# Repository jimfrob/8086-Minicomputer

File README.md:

# 8086 Minicomputer
A basic minicomputer design based on the 8086 CPU

Before anyone starts poking holes in the massive gaps in the logic that Google's AI chat provided in the published documents, I have already started a Rev 2 version of this project to try to get it down to 100x100mm 2-layer boards (to make them ultra-cheap to order from PCBWay). While doing so, I uncovered MANY serious flaws in the design, including, but not limited to, the refresh timing for the DRAM. From here, I'll let my less-experienced self carry on.

Full disclosure up front: I heavily used LLM chats to help me with the design because I'm a complete noob. I just happened to have an 8086 8 MHz CPU lying about, as well as a Specialix I/O4+ quad UART serial card, and I thought I might like to build a minicomputer out of it. This idea was largely inspired by Usagi Electric's TMS9900 minicomputer project. You can check out his projects at https://github.com/Nakazoto

This is, as I've said, a minicomputer. It is my intention that one will only be able to communicate with it over serial terminal, and the serial card I have supports up to four. Storage will be handled by a fairly generic multi-I/O card built around the DLU 270. The eventual ROM code will have these cards in mind. Simply because it's what I have on hand that's 16-bit native, I've gone with the AM27C400 EPROM.

I'm providing the KiCad files I have developed for anyone to use, modify, whatever. I'm quite open to any helpful tips for improving the design. My only minor request is that anyone who makes changes makes sure those changes make it into the wild for everyone to enjoy.

There is absolutely no ROM code at the moment because I don't know any 8086 assembly. I'll be having to learn on the fly. Because of the sheer size of the EPROM, it's entirely possible that I may end up putting the whole OS in there, but this is still early days.

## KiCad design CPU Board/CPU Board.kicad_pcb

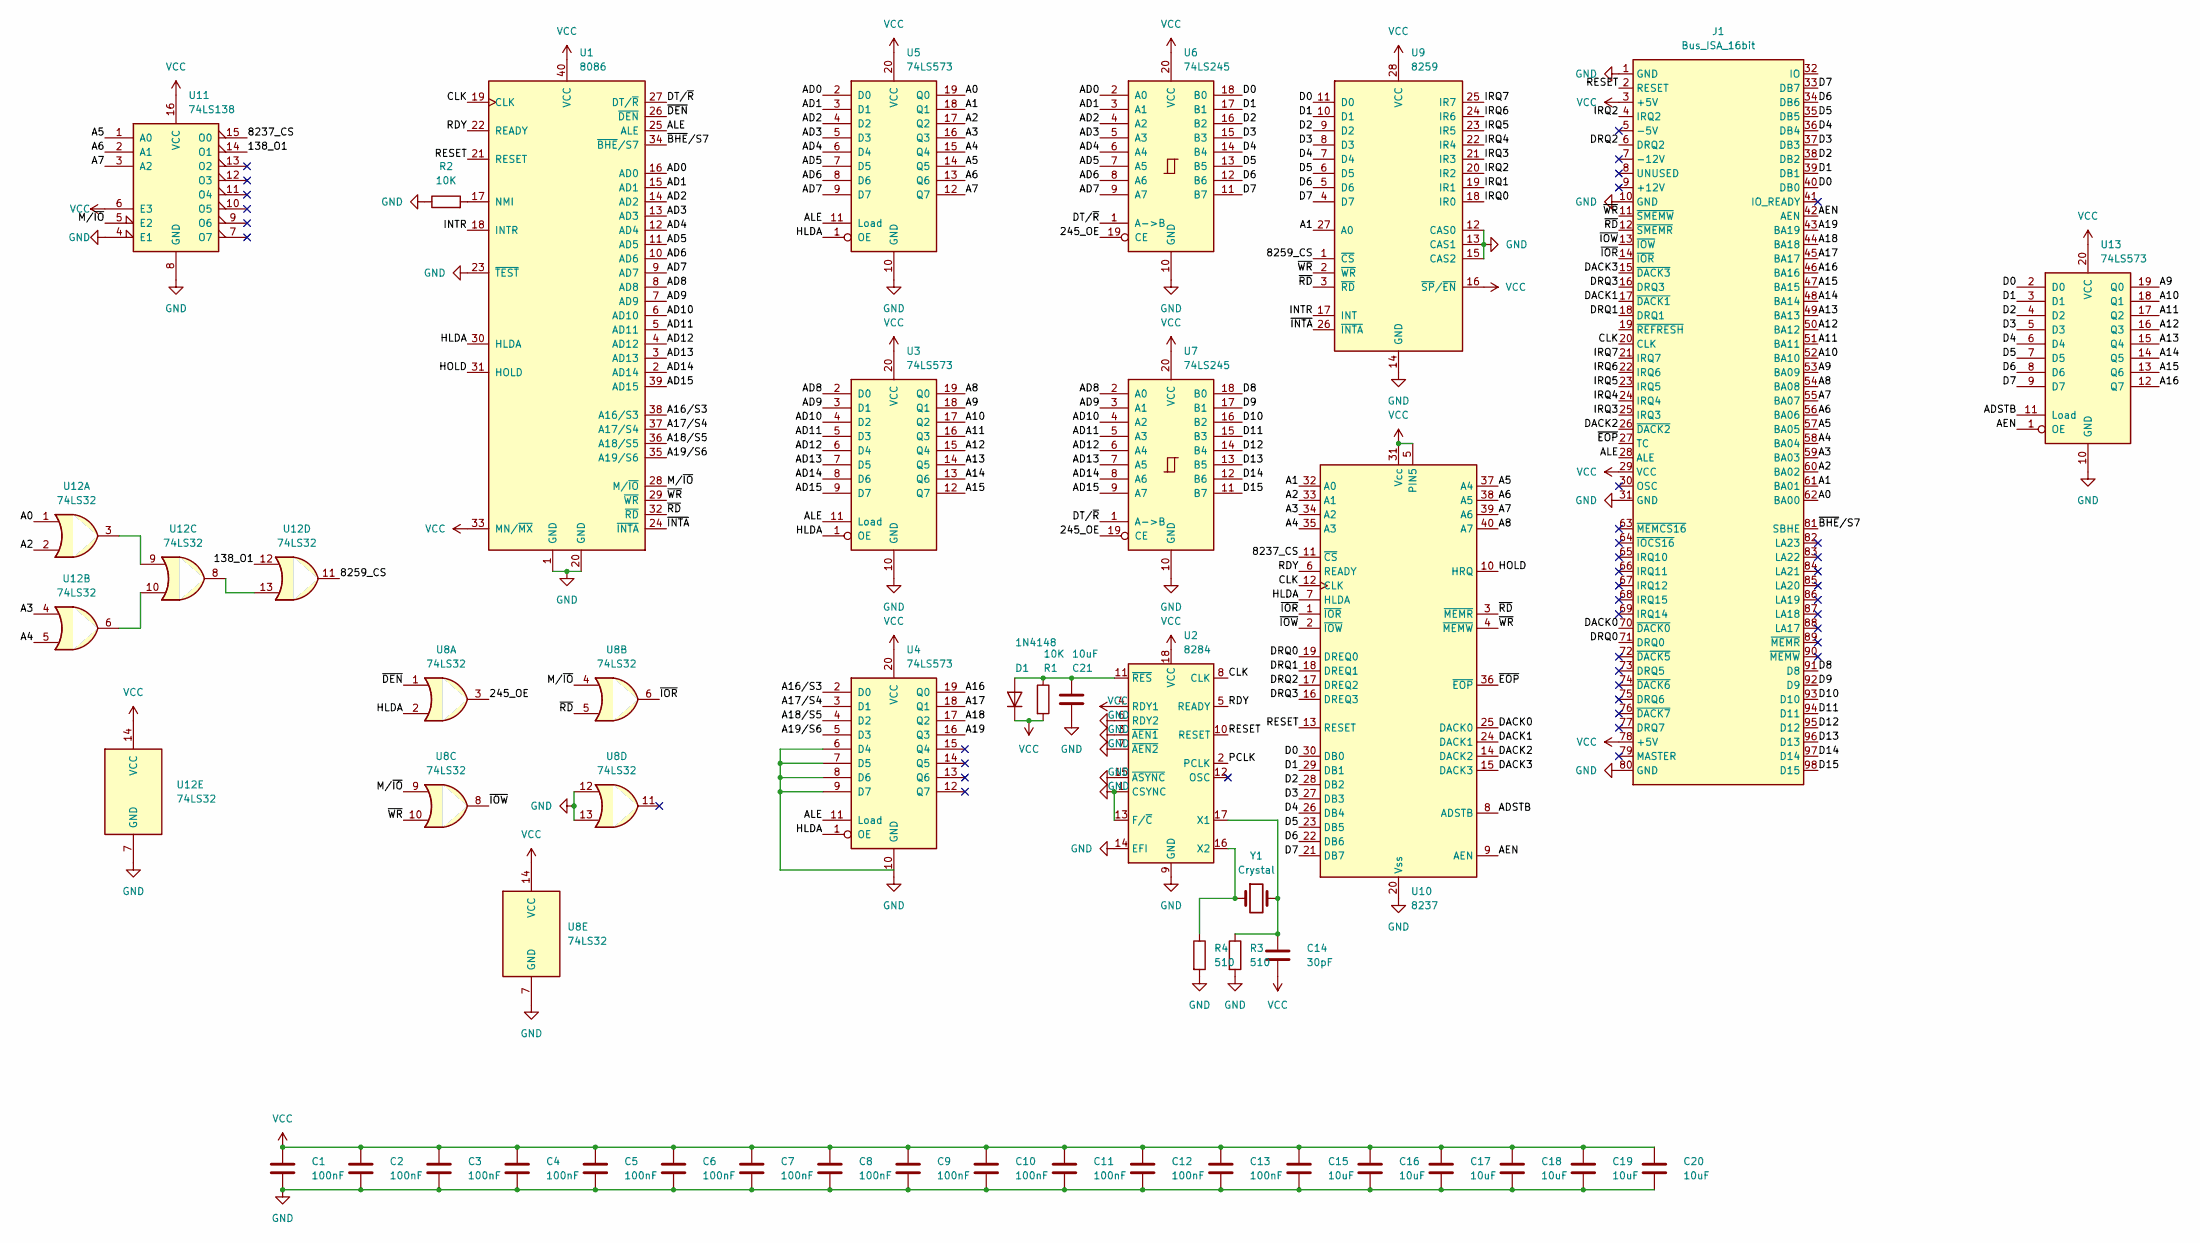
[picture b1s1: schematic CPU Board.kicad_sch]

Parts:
C1, C2, C3, C4, C5, C6, C7, C8, C9, C10, C11, C12, C13: 100nF; C_Disc_D10.0mm_W2.5mm_P5.00mm
C14: 30pF; C_Disc_D10.0mm_W2.5mm_P5.00mm
C15, C16, C17, C18, C19, C20, C21: 10uF; CP_Radial_Tantal_D5.0mm_P2.50mm
D1: 1N4148; D_A-405_P7.62mm_Horizontal
J1: Bus_ISA_16bit; BUS_AT
R1, R2: 10K; R_Axial_DIN0204_L3.6mm_D1.6mm_P7.62mm_Horizontal
R3, R4: 510; R_Axial_DIN0204_L3.6mm_D1.6mm_P7.62mm_Horizontal
U1: 8086; DIP-40_W15.24mm
U2: 8284; DIP-18_W7.62mm
U3, U4, U5, U13: 74LS573; DIP-20_W7.62mm
U6, U7: 74LS245; DIP-20_W7.62mm
U8, U12: 74LS32; DIP-14_W7.62mm
U9: 8259; DIP-28_W15.24mm
U10: 8237; DIP-40_W15.24mm
U11: 74LS138; DIP-16_W7.62mm
Y1: Crystal; Resonator-2Pin_W10.0mm_H5.0mm

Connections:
/138_O1: U11.14 (O1), U12.12
/245_OE: U6.19 (CE), U7.19 (CE), U8.3
/8237_CS: U10.11 (~CS), U11.15 (O0)
/8259_CS: U9.1 (~CS), U12.11
/A0: J1.62 (BA00), U5.19 (Q0), U12.1
/A1: J1.61 (BA01), U5.18 (Q1), U9.27 (A0), U10.32 (A0)
/A2: J1.60 (BA02), U5.17 (Q2), U10.33 (A1), U12.2
/A3: J1.59 (BA03), U5.16 (Q3), U10.34 (A2), U12.4
/A4: J1.58 (BA04), U5.15 (Q4), U10.35 (A3), U12.5
/A5: J1.57 (BA05), U5.14 (Q5), U10.37 (A4), U11.1 (A0)
/A6: J1.56 (BA06), U5.13 (Q6), U10.38 (A5), U11.2 (A1)
/A7: J1.55 (BA07), U5.12 (Q7), U10.39 (A6), U11.3 (A2)
/A8: J1.54 (BA08), U3.19 (Q0), U10.40 (A7)
/A9: J1.53 (BA09), U3.18 (Q1), U13.19 (Q0)
/A10: J1.52 (BA10), U3.17 (Q2), U13.18 (Q1)
/A11: J1.51 (BA11), U3.16 (Q3), U13.17 (Q2)
/A12: J1.50 (BA12), U3.15 (Q4), U13.16 (Q3)
/A13: J1.49 (BA13), U3.14 (Q5), U13.15 (Q4)
/A14: J1.48 (BA14), U3.13 (Q6), U13.14 (Q5)
/A15: J1.47 (BA15), U3.12 (Q7), U13.13 (Q6)
/A16: J1.46 (BA16), U4.19 (Q0), U13.12 (Q7)
/A16/S3: U1.38 (A16/S3), U4.2 (D0)
/A17: J1.45 (BA17), U4.18 (Q1)
/A17/S4: U1.37 (A17/S4), U4.3 (D1)
/A18: J1.44 (BA18), U4.17 (Q2)
/A18/S5: U1.36 (A18/S5), U4.4 (D2)
/A19: J1.43 (BA19), U4.16 (Q3)
/A19/S6: U1.35 (A19/S6), U4.5 (D3)
/AD0: U1.16 (AD0), U5.2 (D0), U6.2 (A0)
/AD1: U1.15 (AD1), U5.3 (D1), U6.3 (A1)
/AD2: U1.14 (AD2), U5.4 (D2), U6.4 (A2)
/AD3: U1.13 (AD3), U5.5 (D3), U6.5 (A3)
/AD4: U1.12 (AD4), U5.6 (D4), U6.6 (A4)
/AD5: U1.11 (AD5), U5.7 (D5), U6.7 (A5)
/AD6: U1.10 (AD6), U5.8 (D6), U6.8 (A6)
/AD7: U1.9 (AD7), U5.9 (D7), U6.9 (A7)
/AD8: U1.8 (AD8), U3.2 (D0), U7.2 (A0)
/AD9: U1.7 (AD9), U3.3 (D1), U7.3 (A1)
/AD10: U1.6 (AD10), U3.4 (D2), U7.4 (A2)
/AD11: U1.5 (AD11), U3.5 (D3), U7.5 (A3)
/AD12: U1.4 (AD12), U3.6 (D4), U7.6 (A4)
/AD13: U1.3 (AD13), U3.7 (D5), U7.7 (A5)
/AD14: U1.2 (AD14), U3.8 (D6), U7.8 (A6)
/AD15: U1.39 (AD15), U3.9 (D7), U7.9 (A7)
/ADSTB: U10.8 (ADSTB), U13.11 (Load)
/AEN: J1.42 (AEN), U10.9 (AEN), U13.1 (OE)
/ALE: J1.28 (ALE), U1.25 (ALE), U3.11 (Load), U4.11 (Load), U5.11 (Load)
/CLK: J1.20 (CLK), U1.19 (CLK), U2.8 (CLK), U10.12 (CLK)
/D0: J1.40 (DB0), U6.18 (B0), U9.11 (D0), U10.30 (DB0), U13.2 (D0)
/D1: J1.39 (DB1), U6.17 (B1), U9.10 (D1), U10.29 (DB1), U13.3 (D1)
/D2: J1.38 (DB2), U6.16 (B2), U9.9 (D2), U10.28 (DB2), U13.4 (D2)
/D3: J1.37 (DB3), U6.15 (B3), U9.8 (D3), U10.27 (DB3), U13.5 (D3)
/D4: J1.36 (DB4), U6.14 (B4), U9.7 (D4), U10.26 (DB4), U13.6 (D4)
/D5: J1.35 (DB5), U6.13 (B5), U9.6 (D5), U10.23 (DB5), U13.7 (D5)
/D6: J1.34 (DB6), U6.12 (B6), U9.5 (D6), U10.22 (DB6), U13.8 (D6)
/D7: J1.33 (DB7), U6.11 (B7), U9.4 (D7), U10.21 (DB7), U13.9 (D7)
/D8: J1.91 (D8), U7.18 (B0)
/D9: J1.92 (D9), U7.17 (B1)
/D10: J1.93 (D10), U7.16 (B2)
/D11: J1.94 (D11), U7.15 (B3)
/D12: J1.95 (D12), U7.14 (B4)
/D13: J1.96 (D13), U7.13 (B5)
/D14: J1.97 (D14), U7.12 (B6)
/D15: J1.98 (D15), U7.11 (B7)
/DACK0: J1.70 (~DACK0), U10.25 (DACK0)
/DACK1: J1.17 (~DACK1), U10.24 (DACK1)
/DACK2: J1.26 (~DACK2), U10.14 (DACK2)
/DACK3: J1.15 (~DACK3), U10.15 (DACK3)
/DRQ0: J1.71 (DRQ0), U10.19 (DREQ0)
/DRQ1: J1.18 (DRQ1), U10.18 (DREQ1)
/DRQ2: J1.6 (DRQ2), U10.17 (DREQ2)
/DRQ3: J1.16 (DRQ3), U10.16 (DREQ3)
/DT/~R: U1.27 (DT/~R), U6.1 (A->B), U7.1 (A->B)
/HLDA: U1.30 (HLDA), U3.1 (OE), U4.1 (OE), U5.1 (OE), U8.2, U10.7 (HLDA)
/HOLD: U1.31 (HOLD), U10.10 (HRQ)
/INTR: U1.18 (INTR), U9.17 (INT)
/IRQ0: U9.18 (IR0)
/IRQ1: U9.19 (IR1)
/IRQ2: J1.4 (IRQ2), U9.20 (IR2)
/IRQ3: J1.25 (IRQ3), U9.21 (IR3)
/IRQ4: J1.24 (IRQ4), U9.22 (IR4)
/IRQ5: J1.23 (IRQ5), U9.23 (IR5)
/IRQ6: J1.22 (IRQ6), U9.24 (IR6)
/IRQ7: J1.21 (IRQ7), U9.25 (IR7)
/M/~IO: U1.28 (M/~IO), U8.4, U8.9, U11.5 (E2)
/PCLK: U2.2 (PCLK)
/RDY: U1.22 (READY), U2.5 (READY), U10.6 (READY)
/RESET: J1.2 (RESET), U1.21 (RESET), U2.10 (RESET), U10.13 (RESET)
/~BHE/S7: J1.81 (SBHE), U1.34 (~BHE/S7)
/~DEN: U1.26 (~DEN), U8.1
/~EOP: J1.27 (TC), U10.36 (~EOP)
/~INTA: U1.24 (~INTA), U9.26 (~INTA)
/~IOR: J1.14 (~IOR), U8.6, U10.1 (~IOR)
/~IOW: J1.13 (~IOW), U8.8, U10.2 (~IOW)
/~RD: J1.12 (~SMEMR), U1.32 (~RD), U8.5, U9.3 (~RD), U10.3 (~MEMR)
/~WR: J1.11 (~SMEMW), U1.29 (~WR), U8.10, U9.2 (~WR), U10.4 (~MEMW)
GND: C1.2, C2.2, C3.2, C4.2, C5.2, C6.2, C7.2, C8.2, C9.2, C10.2, C11.2, C12.2, C13.2, C15.2, C16.2, C17.2, C18.2, C19.2, C20.2, C21.2, J1.1 (GND), J1.10 (GND), J1.31 (GND), J1.80 (GND), R2.1, R3.2, R4.2, U1.1 (GND), U1.20 (GND), U1.23 (~TEST), U2.1 (CSYNC), U2.3 (~AEN1), U2.6 (RDY2), U2.7 (~AEN2), U2.9 (GND), U2.13 (F/~C), U2.14 (EFI), U2.15 (~ASYNC), U3.10 (GND), U4.10 (GND), U5.10 (GND), U6.10 (GND), U7.10 (GND), U8.7 (GND), U8.12, U8.13, U9.12 (CAS0), U9.13 (CAS1), U9.14 (GND), U9.15 (CAS2), U10.20 (Vss), U11.4 (E1), U11.8 (GND), U12.7 (GND), U13.10 (GND)
unnamed: C21.1, D1.2 (A), R1.1, U2.11 (~RES)
unnamed: R2.2, U1.17 (NMI)
unnamed: C14.1, R3.1, U2.17 (X1), Y1.2
unnamed: R4.1, U2.16 (X2), Y1.1
unnamed: U4.6 (D4), U4.7 (D5), U4.8 (D6), U4.9 (D7)
unnamed: U12.3, U12.9
unnamed: U12.6, U12.10
unnamed: U12.8, U12.13
VCC: C1.1, C2.1, C3.1, C4.1, C5.1, C6.1, C7.1, C8.1, C9.1, C10.1, C11.1, C12.1, C13.1, C14.2, C15.1, C16.1, C17.1, C18.1, C19.1, C20.1, D1.1 (K), J1.3 (+5V), J1.29 (VCC), J1.78 (+5V), R1.2, U1.33 (MN/~MX), U1.40 (VCC), U2.4 (RDY1), U2.18 (VCC), U3.20 (VCC), U4.20 (VCC), U5.20 (VCC), U6.20 (VCC), U7.20 (VCC), U8.14 (VCC), U9.16 (~SP/~EN), U9.28 (VCC), U10.5 (PIN5), U10.31 (Vcc), U11.6 (E3), U11.16 (VCC), U12.14 (VCC), U13.20 (VCC)

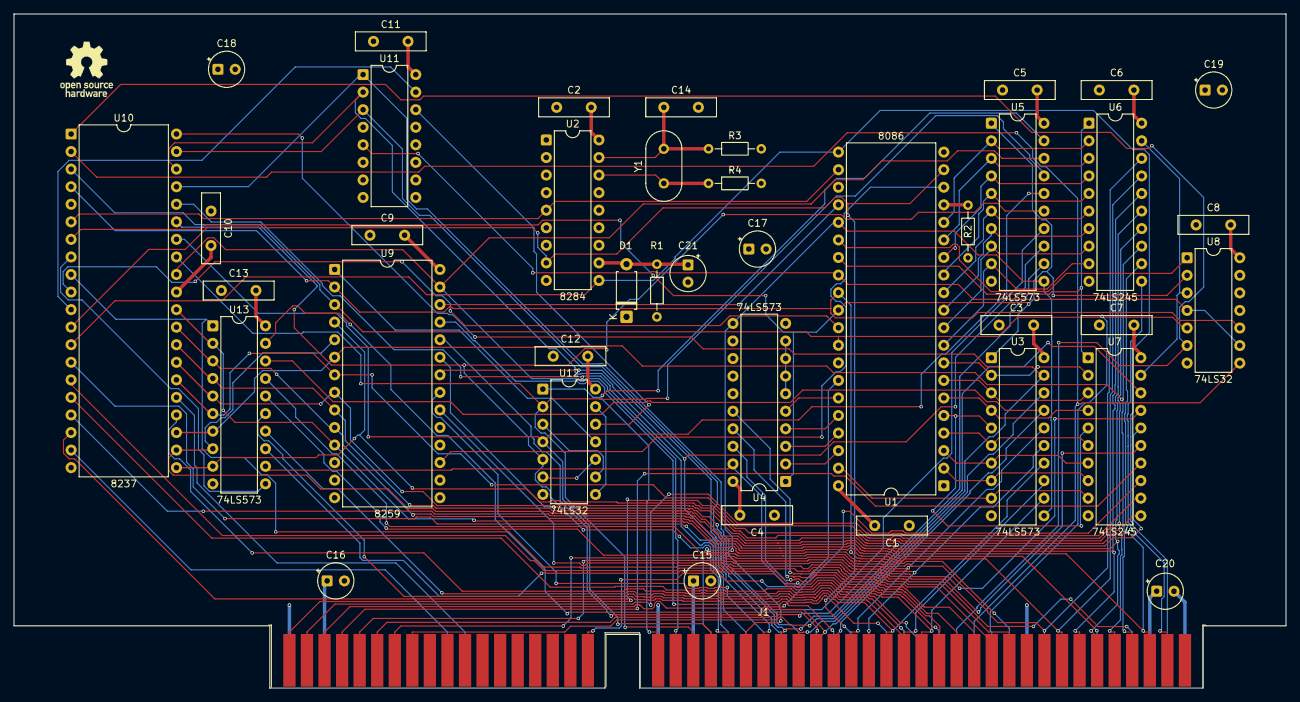
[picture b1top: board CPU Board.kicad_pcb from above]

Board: 4 copper layers, 184.0 x 97.5 mm, 41 parts (0 on the bottom side), 103 nets.

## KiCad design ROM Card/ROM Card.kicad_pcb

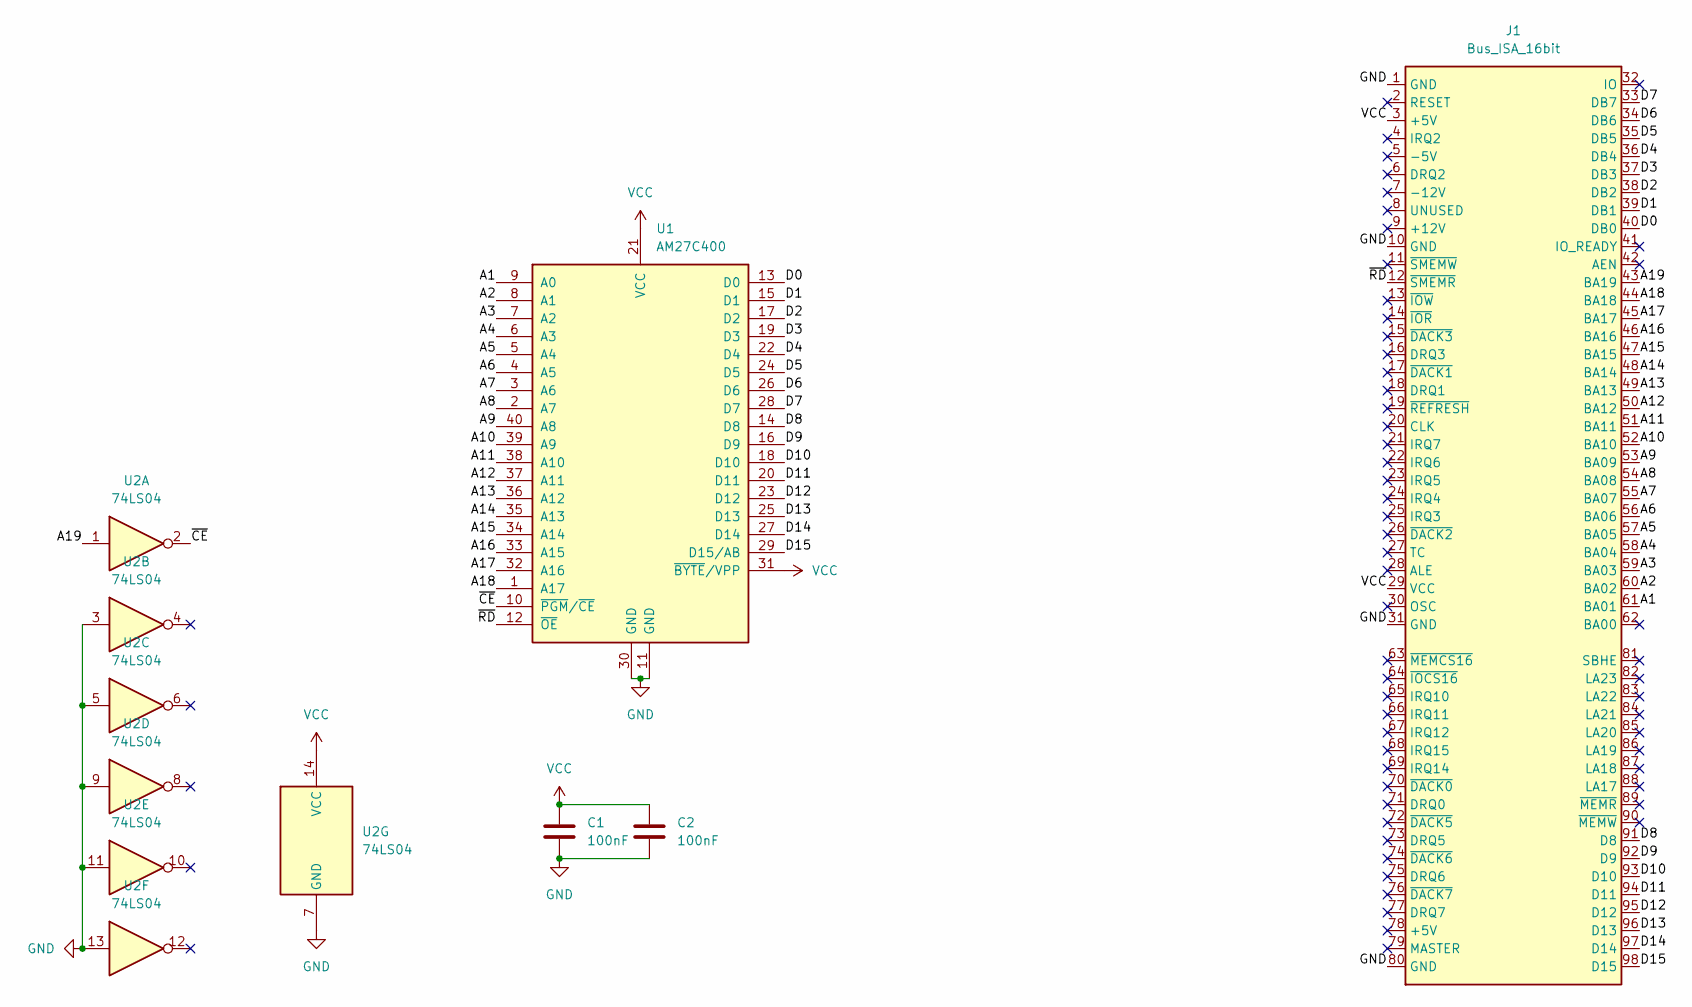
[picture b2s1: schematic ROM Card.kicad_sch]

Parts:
C1, C2: 100nF; C_Disc_D10.0mm_W2.5mm_P5.00mm
J1: Bus_ISA_16bit; BUS_AT
U1: AM27C400; DIP-40_W15.24mm
U2: 74LS04; DIP-14_W7.62mm

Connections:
/A1: J1.61 (BA01), U1.9 (A0)
/A2: J1.60 (BA02), U1.8 (A1)
/A3: J1.59 (BA03), U1.7 (A2)
/A4: J1.58 (BA04), U1.6 (A3)
/A5: J1.57 (BA05), U1.5 (A4)
/A6: J1.56 (BA06), U1.4 (A5)
/A7: J1.55 (BA07), U1.3 (A6)
/A8: J1.54 (BA08), U1.2 (A7)
/A9: J1.53 (BA09), U1.40 (A8)
/A10: J1.52 (BA10), U1.39 (A9)
/A11: J1.51 (BA11), U1.38 (A10)
/A12: J1.50 (BA12), U1.37 (A11)
/A13: J1.49 (BA13), U1.36 (A12)
/A14: J1.48 (BA14), U1.35 (A13)
/A15: J1.47 (BA15), U1.34 (A14)
/A16: J1.46 (BA16), U1.33 (A15)
/A17: J1.45 (BA17), U1.32 (A16)
/A18: J1.44 (BA18), U1.1 (A17)
/A19: J1.43 (BA19), U2.1
/D0: J1.40 (DB0), U1.13 (D0)
/D1: J1.39 (DB1), U1.15 (D1)
/D2: J1.38 (DB2), U1.17 (D2)
/D3: J1.37 (DB3), U1.19 (D3)
/D4: J1.36 (DB4), U1.22 (D4)
/D5: J1.35 (DB5), U1.24 (D5)
/D6: J1.34 (DB6), U1.26 (D6)
/D7: J1.33 (DB7), U1.28 (D7)
/D8: J1.91 (D8), U1.14 (D8)
/D9: J1.92 (D9), U1.16 (D9)
/D10: J1.93 (D10), U1.18 (D10)
/D11: J1.94 (D11), U1.20 (D11)
/D12: J1.95 (D12), U1.23 (D12)
/D13: J1.96 (D13), U1.25 (D13)
/D14: J1.97 (D14), U1.27 (D14)
/D15: J1.98 (D15), U1.29 (D15/AB)
/~CE: U1.10 (~PGM/~CE), U2.2
/~RD: J1.12 (~SMEMR), U1.12 (~OE)
GND: C1.2, C2.2, J1.1 (GND), J1.10 (GND), J1.31 (GND), J1.80 (GND), U1.11 (GND), U1.30 (GND), U2.3, U2.5, U2.7 (GND), U2.9, U2.11, U2.13
VCC: C1.1, C2.1, J1.3 (+5V), J1.29 (VCC), U1.21 (VCC), U1.31 (~BYTE/VPP), U2.14 (VCC)

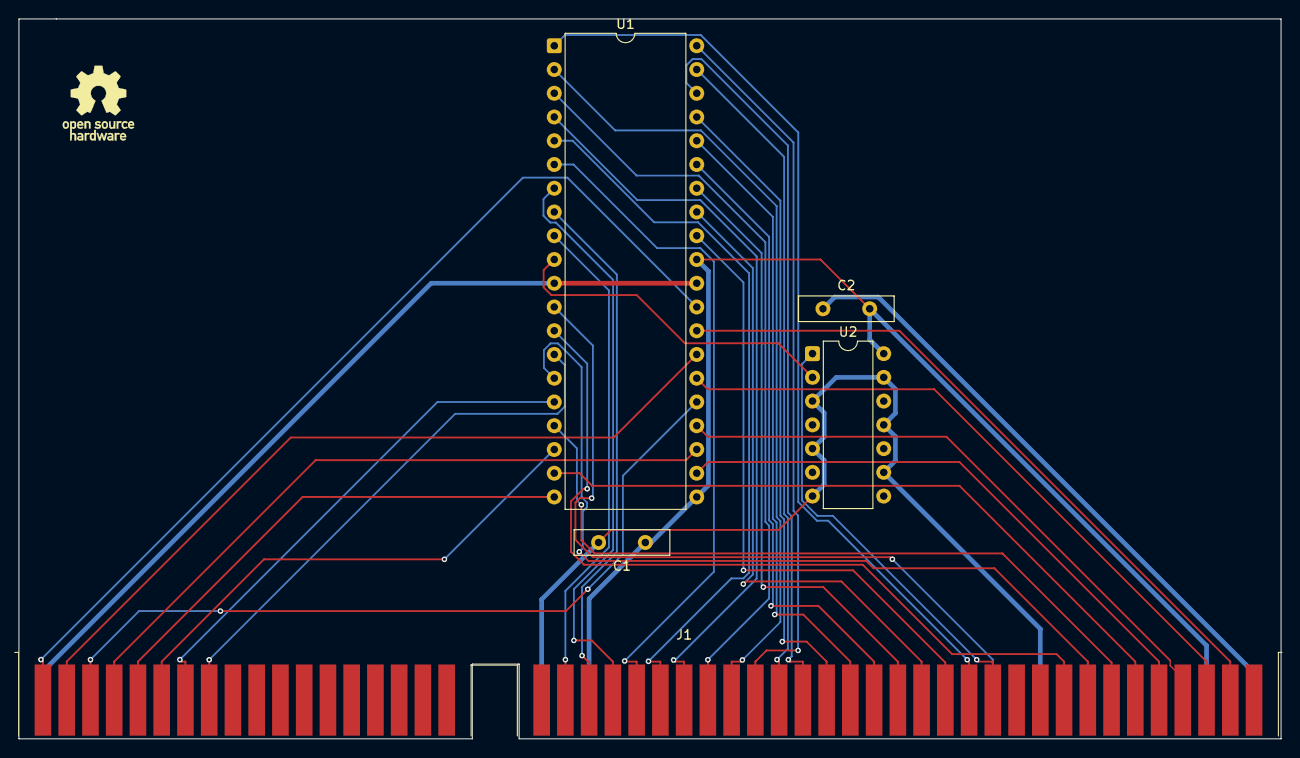
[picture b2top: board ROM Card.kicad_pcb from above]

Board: 2 copper layers, 135.0 x 77.0 mm, 5 parts (0 on the bottom side), 39 nets.

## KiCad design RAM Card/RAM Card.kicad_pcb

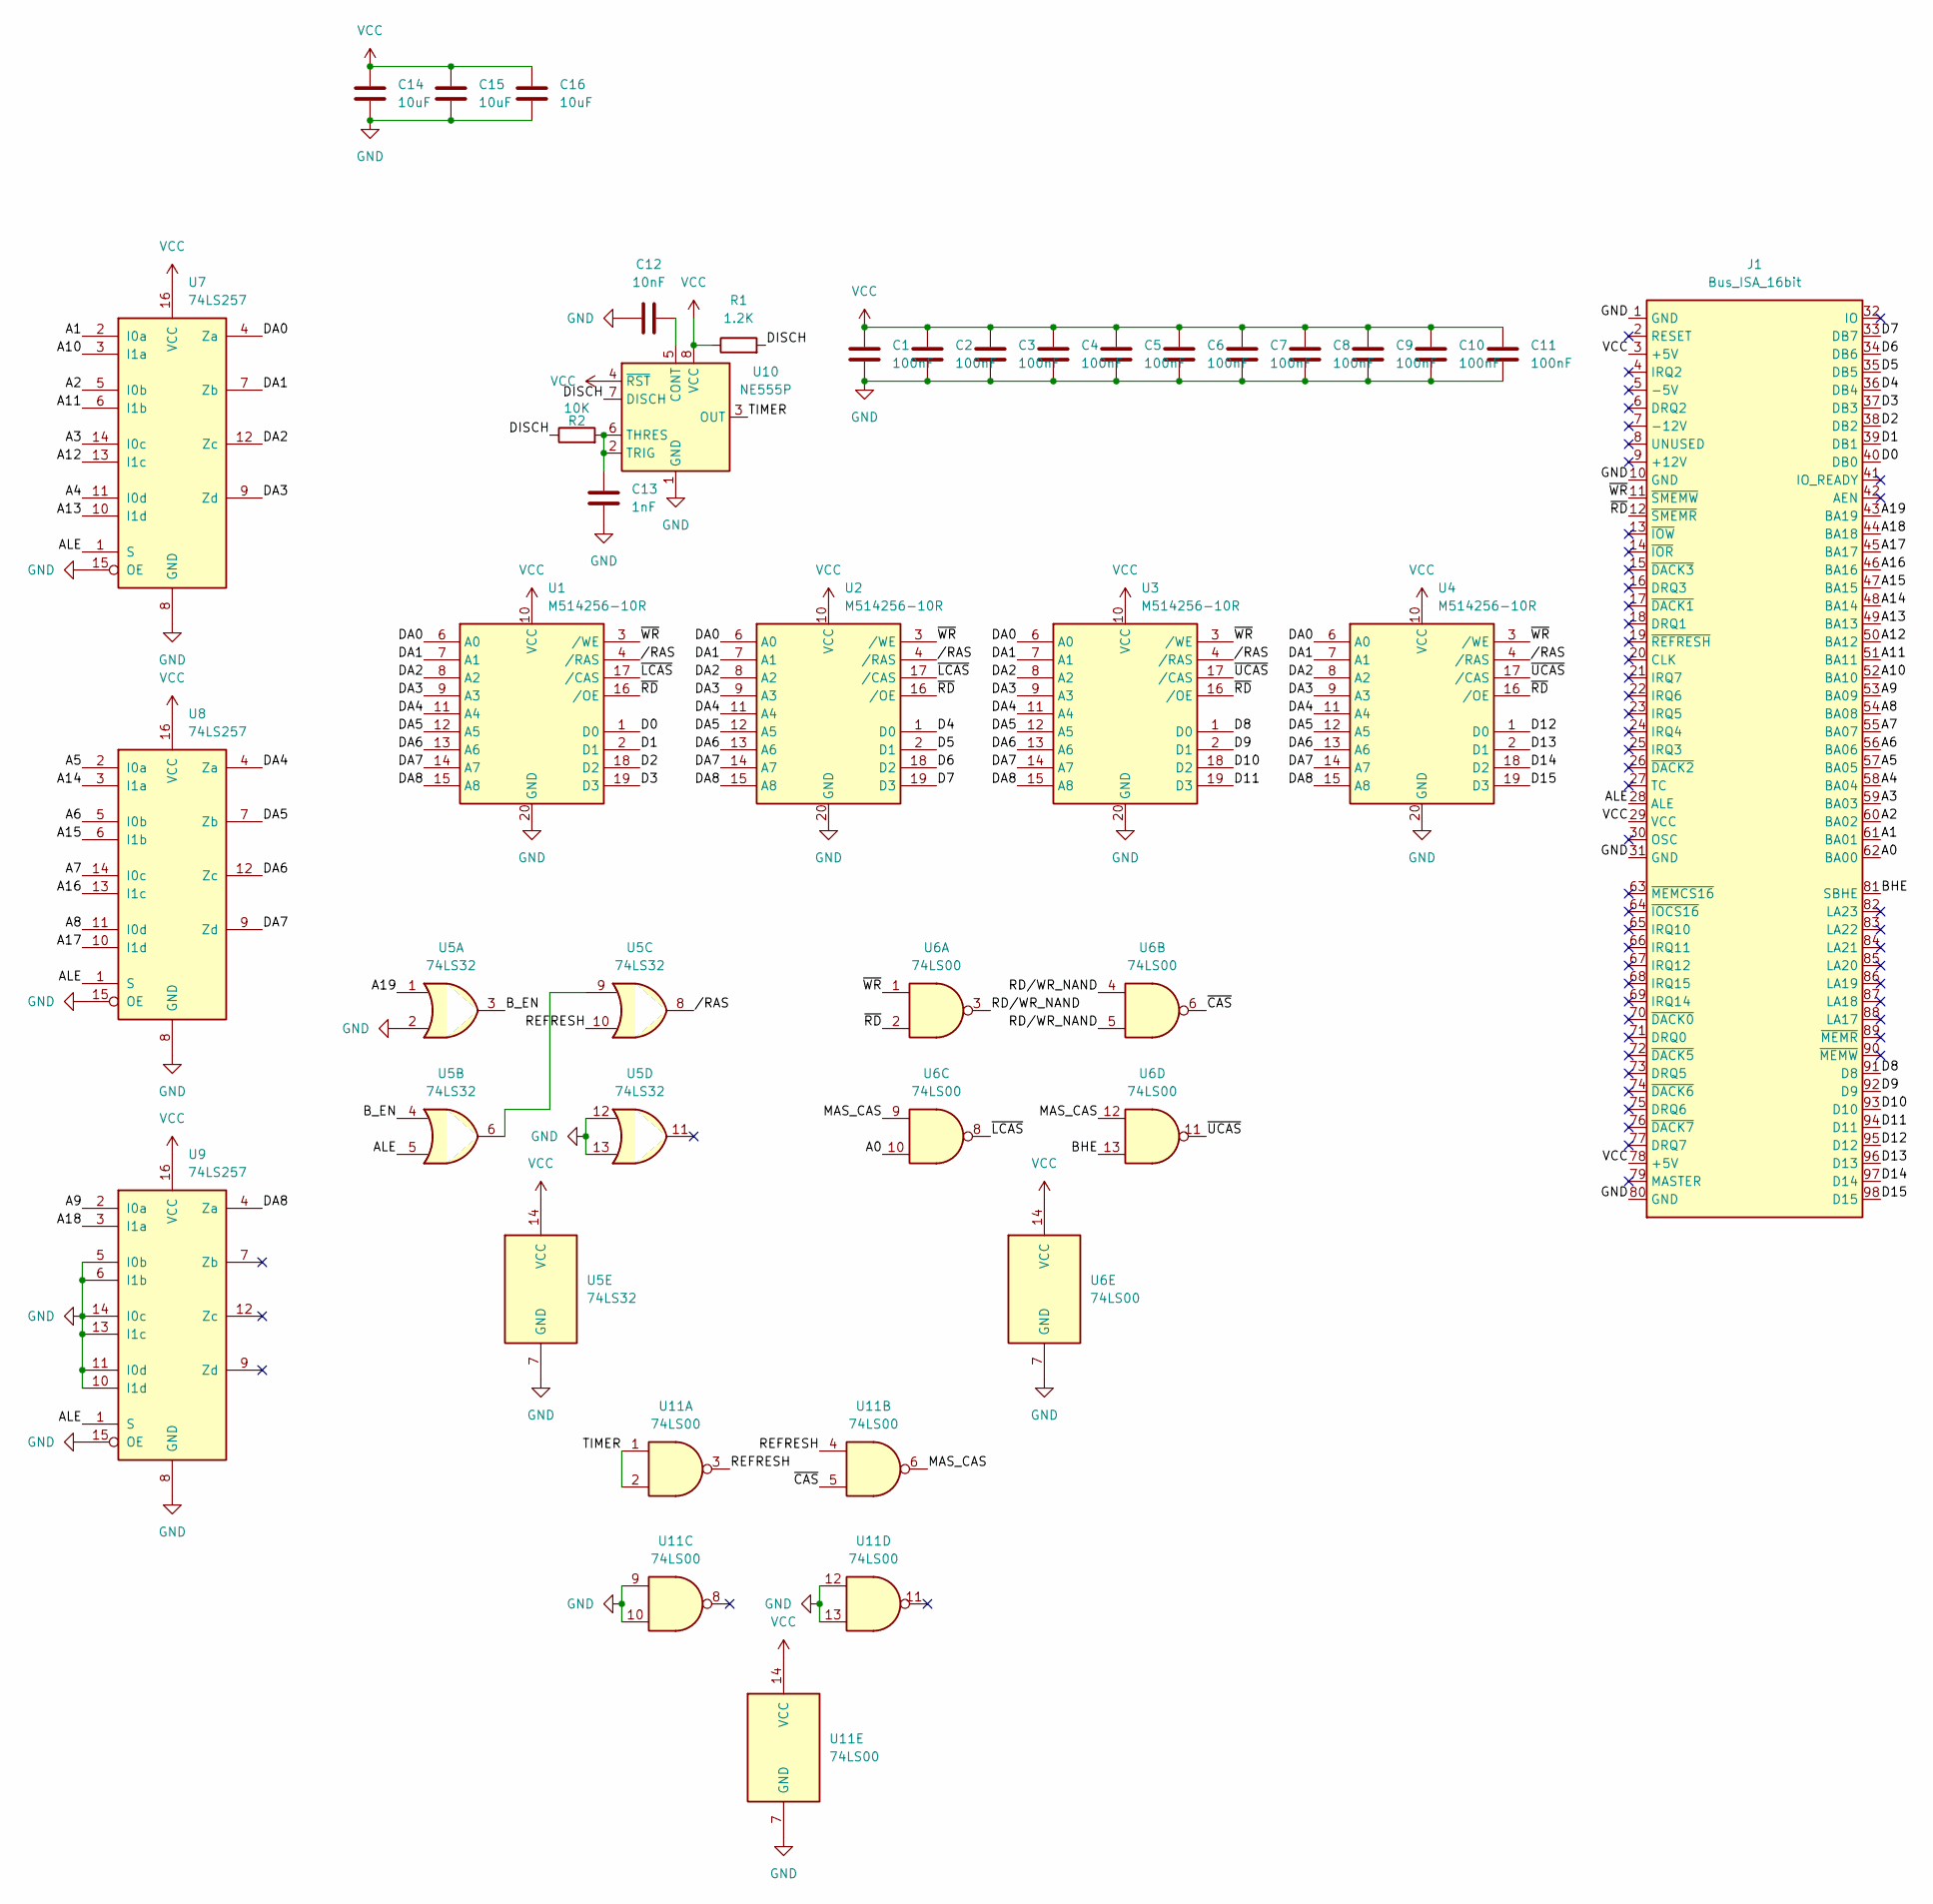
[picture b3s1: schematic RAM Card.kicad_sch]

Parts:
C1, C2, C3, C4, C5, C6, C7, C8, C9, C10, C11: 100nF; C_Disc_D10.0mm_W2.5mm_P5.00mm
C12: 10nF; C_Disc_D10.0mm_W2.5mm_P5.00mm
C13: 1nF; C_Disc_D10.0mm_W2.5mm_P5.00mm
C14, C15, C16: 10uF; CP_Radial_Tantal_D5.0mm_P2.50mm
J1: Bus_ISA_16bit; BUS_AT
R1: 1.2K; R_Axial_DIN0204_L3.6mm_D1.6mm_P7.62mm_Horizontal
R2: 10K; R_Axial_DIN0204_L3.6mm_D1.6mm_P7.62mm_Horizontal
U1, U2, U3, U4: M514256-10R; DIP-20_W7.62mm; Manufacturer Part KM44C4000C
U5: 74LS32; DIP-14_W7.62mm
U6, U11: 74LS00; DIP-14_W7.62mm
U7, U8, U9: 74LS257; DIP-16_W7.62mm
U10: NE555P; DIP-8_W7.62mm

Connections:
/A0: J1.62 (BA00), U6.10
/A1: J1.61 (BA01), U7.2 (I0a)
/A2: J1.60 (BA02), U7.5 (I0b)
/A3: J1.59 (BA03), U7.14 (I0c)
/A4: J1.58 (BA04), U7.11 (I0d)
/A5: J1.57 (BA05), U8.2 (I0a)
/A6: J1.56 (BA06), U8.5 (I0b)
/A7: J1.55 (BA07), U8.14 (I0c)
/A8: J1.54 (BA08), U8.11 (I0d)
/A9: J1.53 (BA09), U9.2 (I0a)
/A10: J1.52 (BA10), U7.3 (I1a)
/A11: J1.51 (BA11), U7.6 (I1b)
/A12: J1.50 (BA12), U7.13 (I1c)
/A13: J1.49 (BA13), U7.10 (I1d)
/A14: J1.48 (BA14), U8.3 (I1a)
/A15: J1.47 (BA15), U8.6 (I1b)
/A16: J1.46 (BA16), U8.13 (I1c)
/A17: J1.45 (BA17), U8.10 (I1d)
/A18: J1.44 (BA18), U9.3 (I1a)
/A19: J1.43 (BA19), U5.1
/ALE: J1.28 (ALE), U5.5, U7.1 (S), U8.1 (S), U9.1 (S)
/BHE: J1.81 (SBHE), U6.13
/B_EN: U5.3, U5.4
/D0: J1.40 (DB0), U1.1 (D0)
/D1: J1.39 (DB1), U1.2 (D1)
/D2: J1.38 (DB2), U1.18 (D2)
/D3: J1.37 (DB3), U1.19 (D3)
/D4: J1.36 (DB4), U2.1 (D0)
/D5: J1.35 (DB5), U2.2 (D1)
/D6: J1.34 (DB6), U2.18 (D2)
/D7: J1.33 (DB7), U2.19 (D3)
/D8: J1.91 (D8), U3.1 (D0)
/D9: J1.92 (D9), U3.2 (D1)
/D10: J1.93 (D10), U3.18 (D2)
/D11: J1.94 (D11), U3.19 (D3)
/D12: J1.95 (D12), U4.1 (D0)
/D13: J1.96 (D13), U4.2 (D1)
/D14: J1.97 (D14), U4.18 (D2)
/D15: J1.98 (D15), U4.19 (D3)
/DA0: U1.6 (A0), U2.6 (A0), U3.6 (A0), U4.6 (A0), U7.4 (Za)
/DA1: U1.7 (A1), U2.7 (A1), U3.7 (A1), U4.7 (A1), U7.7 (Zb)
/DA2: U1.8 (A2), U2.8 (A2), U3.8 (A2), U4.8 (A2), U7.12 (Zc)
/DA3: U1.9 (A3), U2.9 (A3), U3.9 (A3), U4.9 (A3), U7.9 (Zd)
/DA4: U1.11 (A4), U2.11 (A4), U3.11 (A4), U4.11 (A4), U8.4 (Za)
/DA5: U1.12 (A5), U2.12 (A5), U3.12 (A5), U4.12 (A5), U8.7 (Zb)
/DA6: U1.13 (A6), U2.13 (A6), U3.13 (A6), U4.13 (A6), U8.12 (Zc)
/DA7: U1.14 (A7), U2.14 (A7), U3.14 (A7), U4.14 (A7), U8.9 (Zd)
/DA8: U1.15 (A8), U2.15 (A8), U3.15 (A8), U4.15 (A8), U9.4 (Za)
/DISCH: R1.2, R2.1, U10.7 (DISCH)
/MAS_CAS: U6.9, U6.12, U11.6
/RD/WR_NAND: U6.3, U6.4, U6.5
/REFRESH: U5.10, U11.3, U11.4
/TIMER: U10.3 (OUT), U11.1, U11.2
//RAS: U1.4 (/RAS), U2.4 (/RAS), U3.4 (/RAS), U4.4 (/RAS), U5.8
/~CAS: U6.6, U11.5
/~LCAS: U1.17 (/CAS), U2.17 (/CAS), U6.8
/~RD: J1.12 (~SMEMR), U1.16 (/OE), U2.16 (/OE), U3.16 (/OE), U4.16 (/OE), U6.2
/~UCAS: U3.17 (/CAS), U4.17 (/CAS), U6.11
/~WR: J1.11 (~SMEMW), U1.3 (/WE), U2.3 (/WE), U3.3 (/WE), U4.3 (/WE), U6.1
GND: C1.2, C2.2, C3.2, C4.2, C5.2, C6.2, C7.2, C8.2, C9.2, C10.2, C11.2, C12.1, C13.2, C14.2, C15.2, C16.2, J1.1 (GND), J1.10 (GND), J1.31 (GND), J1.80 (GND), U1.20 (GND), U2.20 (GND), U3.20 (GND), U4.20 (GND), U5.2, U5.7 (GND), U5.12, U5.13, U6.7 (GND), U7.8 (GND), U7.15 (OE), U8.8 (GND), U8.15 (OE), U9.5 (I0b), U9.6 (I1b), U9.8 (GND), U9.10 (I1d), U9.11 (I0d), U9.13 (I1c), U9.14 (I0c), U9.15 (OE), U10.1 (GND), U11.7 (GND), U11.9, U11.10, U11.12, U11.13
unnamed: U5.6, U5.9
unnamed: C12.2, U10.5 (CONT)
unnamed: C13.1, R2.2, U10.2 (TRIG), U10.6 (THRES)
VCC: C1.1, C2.1, C3.1, C4.1, C5.1, C6.1, C7.1, C8.1, C9.1, C10.1, C11.1, C14.1, C15.1, C16.1, J1.3 (+5V), J1.29 (VCC), J1.78 (+5V), R1.1, U1.10 (VCC), U2.10 (VCC), U3.10 (VCC), U4.10 (VCC), U5.14 (VCC), U6.14 (VCC), U7.16 (VCC), U8.16 (VCC), U9.16 (VCC), U10.4 (~RST), U10.8 (VCC), U11.14 (VCC)

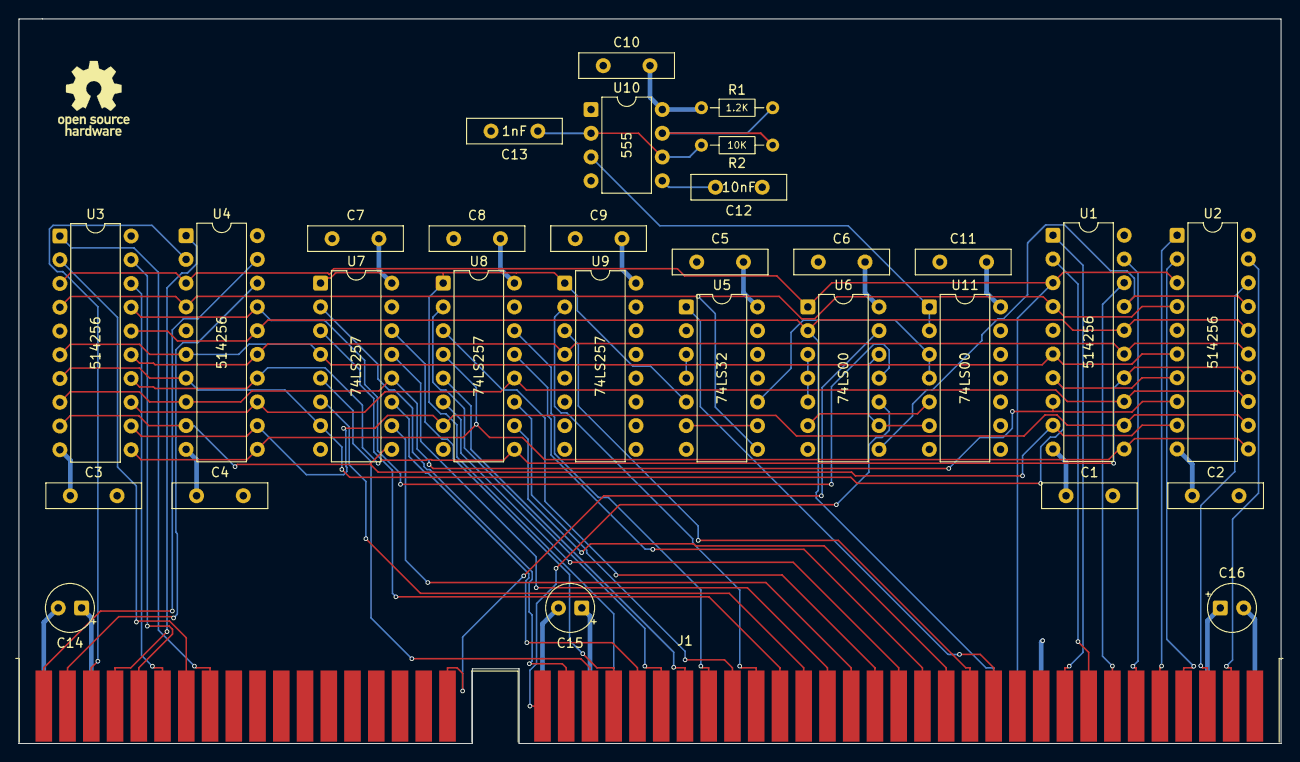
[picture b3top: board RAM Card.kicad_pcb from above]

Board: 4 copper layers, 135.0 x 77.5 mm, 30 parts (0 on the bottom side), 64 nets.
